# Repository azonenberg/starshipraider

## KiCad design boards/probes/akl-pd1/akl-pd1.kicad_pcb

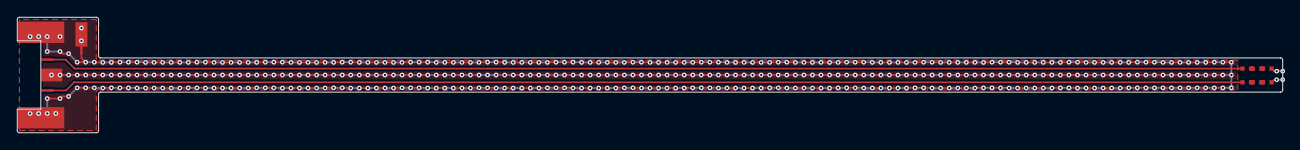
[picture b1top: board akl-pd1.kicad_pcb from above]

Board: 2 copper layers, 148.0 x 13.5 mm, 8 parts (0 on the bottom side), 7 nets.

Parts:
J1: 3211-60087; CONN_SMPM_DUAL_AMPHENOL_3211-60087
J3: GNDSOCKET; CONN_MILLMAX_0339_EDGELAUNCH
R1, R2: FC0402E50R0BTT0; EIA_0402_RES_NOSILK_FLIPCHIP
R3, R4, R5, R6: FC0402E2000BTT0; EIA_0402_RES_NOSILK_FLIPCHIP

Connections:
/GND: J1.3, J3.1
/IN_N: J1.2, R2.2
/IN_P: J1.1, R1.2
unnamed: R1.1, R3.2
unnamed: R2.1, R4.2
unnamed: R3.1, R5.2
unnamed: R4.1, R6.2

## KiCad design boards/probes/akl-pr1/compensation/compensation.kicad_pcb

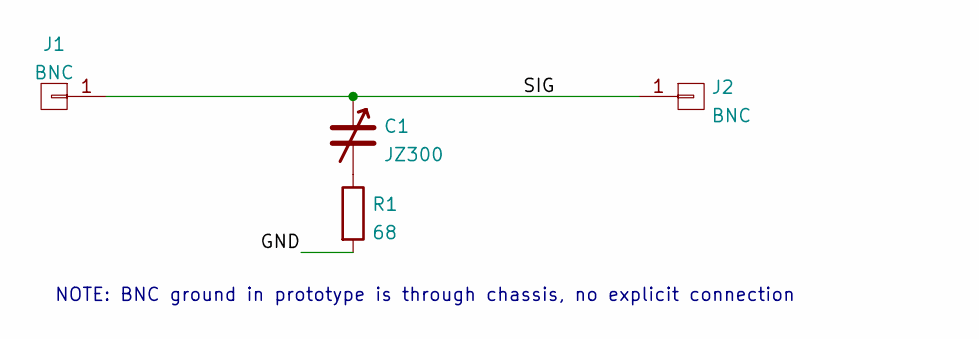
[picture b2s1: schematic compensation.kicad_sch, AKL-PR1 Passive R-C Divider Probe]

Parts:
C1: JZ300; CAP_TRIM_KNOWLES_JZ
J1, J2: BNC; TESTPOINT_BARETRACE_328UM
R1: 68; EIA_0402_RES_NOSILK

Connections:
/GND: R1.2
/SIG: C1.1, J1.1, J2.1
unnamed: C1.2, R1.1

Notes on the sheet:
NOTE: BNC ground in prototype is through chassis, no explicit connection

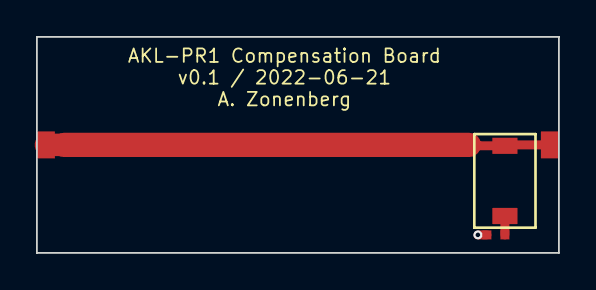
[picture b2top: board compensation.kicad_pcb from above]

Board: 2 copper layers, 29.0 x 12.0 mm, 4 parts (0 on the bottom side), 2 nets.

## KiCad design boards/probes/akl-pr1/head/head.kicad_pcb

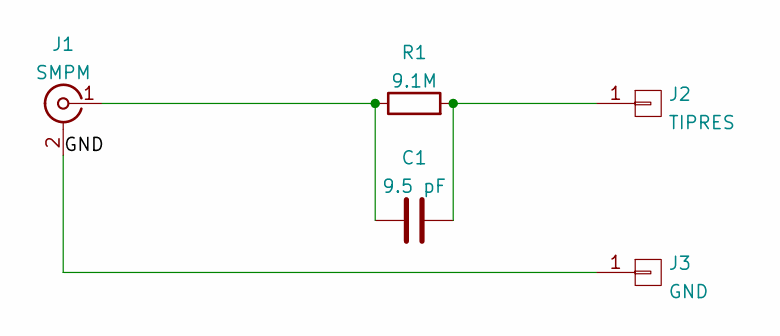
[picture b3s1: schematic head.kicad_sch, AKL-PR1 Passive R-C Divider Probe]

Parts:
C1: 9.5 pF; EIA_0402_CAP_NOSILK
J1: SMPM; CONN_SMPM_AMPHENOL_925-169J-51PT
J2: TIPRES; TESTPOINT_BARETRACE_328UM
J3: GND; TESTPOINT_BARETRACE_328UM
R1: 9.1M; EIA_0402_CAP_NOSILK

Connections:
/GND: J1.2 (Ext), J3.1
unnamed: C1.1, J1.1 (In), R1.1
unnamed: C1.2, J2.1, R1.2

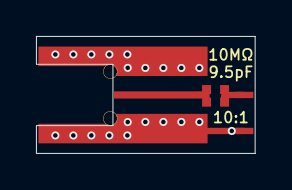
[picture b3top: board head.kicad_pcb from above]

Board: 4 copper layers, 12.1 x 6.5 mm, 5 parts (0 on the bottom side), 3 nets.

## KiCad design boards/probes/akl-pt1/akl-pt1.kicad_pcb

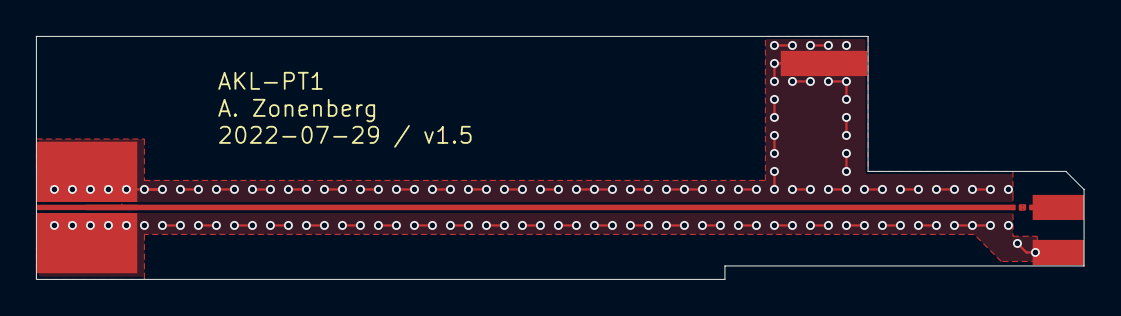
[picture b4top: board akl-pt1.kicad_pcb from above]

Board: 4 copper layers, 58.2 x 13.5 mm, 6 parts (0 on the bottom side), 4 nets.

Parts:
J1: 901-10511-3; CONN_SMA_EDGE_AMPHENOL_901_10511_3
J2, J3, J4: PROBETIP; CONN_MILLMAX_0339_EDGELAUNCH
R1: CH02016-200RGFTA; EIA_02016_RES_NOSILK_FLIPCHIP
R2: CH02016-250RGFTA; EIA_02016_RES_NOSILK_FLIPCHIP

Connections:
/GND: J1.2, J3.1, J4.1
unnamed: J1.1, R1.2
unnamed: J2.1, R2.1
unnamed: R1.1, R2.2

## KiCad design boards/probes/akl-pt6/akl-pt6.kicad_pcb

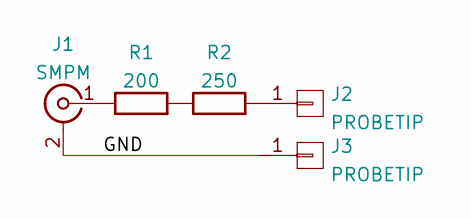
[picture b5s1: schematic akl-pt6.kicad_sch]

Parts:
J1: SMPM; CONN_SMPM_AMPHENOL_925-169J-51PT_SHORT
J2, J3: PROBETIP; CONN_MILLMAX_0339_EDGELAUNCH
R1: 200; EIA_02016_RES_NOSILK_FLIPCHIP
R2: 250; EIA_02016_RES_NOSILK_FLIPCHIP

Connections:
/GND: J1.2 (Ext), J3.1
unnamed: J1.1 (In), R1.1
unnamed: J2.1, R2.2
unnamed: R1.2, R2.1

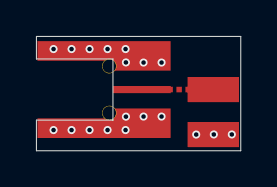
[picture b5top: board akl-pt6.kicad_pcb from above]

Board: 4 copper layers, 11.3 x 6.4 mm, 5 parts (0 on the bottom side), 4 nets.

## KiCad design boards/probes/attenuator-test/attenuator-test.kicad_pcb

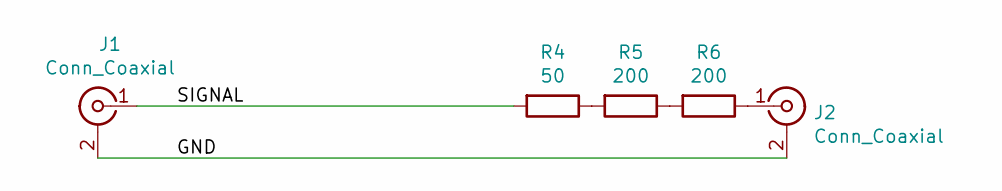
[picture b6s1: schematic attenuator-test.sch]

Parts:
J1, J2: Conn_Coaxial; CONN_SMA_EDGE_AMPHENOL_901_10511_3
R4: 50; EIA_0402_RES_NOSILK_FLIPCHIP
R5, R6: 200; EIA_0402_RES_NOSILK_FLIPCHIP

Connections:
/GND: J1.2 (Ext), J2.2 (Ext)
/SIGNAL: J1.1 (In), R4.2
unnamed: J2.1 (In), R6.1
unnamed: R4.1, R5.2
unnamed: R5.1, R6.2

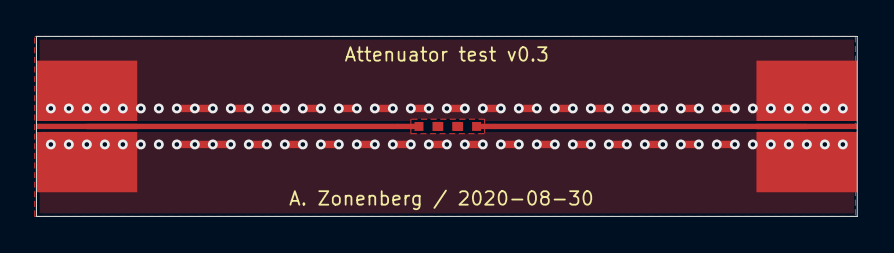
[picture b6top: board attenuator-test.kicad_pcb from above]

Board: 4 copper layers, 45.6 x 10.0 mm, 5 parts (0 on the bottom side), 5 nets.
